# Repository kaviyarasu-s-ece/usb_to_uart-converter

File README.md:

# usb_to_uart-converter
This is type of circuit which converts the data from USB to UART(Universal Asynchronous Receive and Transmit)

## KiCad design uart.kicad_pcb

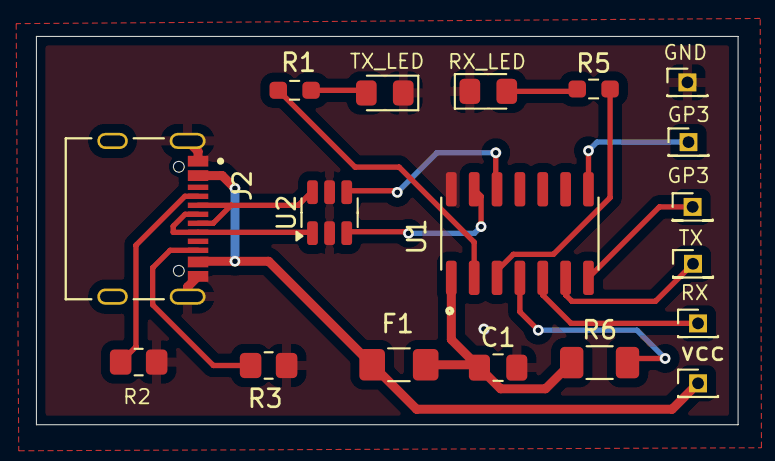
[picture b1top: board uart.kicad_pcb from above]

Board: 2 copper layers, 39.0 x 21.6 mm, 18 parts (0 on the bottom side), 18 nets.

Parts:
C1: C; C_0805_2012Metric_Pad1.18x1.45mm_HandSolder
F1: Fuse; Fuse_1206_3216Metric_Pad1.42x1.75mm_HandSolder
J2: USB_C_Receptacle_USB2.0_14P; HRO_TYPE-C-31-M-12
R1, R5: 330; R_0603_1608Metric_Pad0.98x0.95mm_HandSolder
R2, R3: 5.1k; R_0805_2012Metric_Pad1.20x1.40mm_HandSolder
R6: 10K; R_1206_3216Metric_Pad1.30x1.75mm_HandSolder
RX_LED: RX_LED; LED_0805_2012Metric_Pad1.15x1.40mm_HandSolder
TP1: TX; PinHeader_1x01_P1.27mm_Vertical
TP2: RX; PinHeader_1x01_P1.27mm_Vertical
TP3, TP4: GP3; PinHeader_1x01_P1.27mm_Vertical
TP5: power_output; PinHeader_1x01_P1.27mm_Vertical
TP6: GND; PinHeader_1x01_P1.27mm_Vertical
TX_LED: TX_LED; LED_0805_2012Metric_Pad1.15x1.40mm_HandSolder
U1: SOIC127P600X175-14N; MCP2221A-I_SL
U2: USBLC6-2SC6; SOT-23-6

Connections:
+5V: F1.1, J2.A4 (VBUS), TP5.1
/D++: U1.13 (D+), U2.3 (I/O2)
/D--: U1.12 (D-), U2.4 (I/O2)
/gp0: R1.2, U1.2 (GP0)
/gp1: R5.2, U1.3 (GP1)
/ip: C1.1, F1.2, R6.1, U1.1 (VDD)
/tie1: J2.A6 (D+), J2.B6 (D+), U2.1 (I/O1)
/tie2: J2.A7 (D-), J2.B7 (D-), U2.6 (I/O1)
GND: C1.2, J2.A1 (GND), J2.S1 (SHIELD), J2.S2, R2.2, R3.2, RX_LED.1 (K), TP6.1, TX_LED.1 (K), U1.14 (VSS), U2.2 (GND), U2.5 (VBUS)
unnamed: R1.1, TX_LED.2 (A)
unnamed: R5.1, RX_LED.2 (A)
unnamed: J2.A5 (CC1), R2.1
unnamed: J2.B5 (CC2), R3.1
unnamed: TP3.1, U1.7 (GP2)
unnamed: TP4.1, U1.8 (GP3)
unnamed: TP2.1, U1.5 (URX)
unnamed: TP1.1, U1.6 (UTX)
unnamed: R6.2, U1.4 (~RST)

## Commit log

2026-03-27 Fix typo in README description
2026-03-28 Delete uart.kicad_pro
    i will update new file
2026-03-28 Delete uart.kicad_pcb
    i will update new file
2026-03-28 Delete uart.kicad_sch
    i will update new file
